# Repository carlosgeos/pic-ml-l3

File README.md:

# PIC ML-L3

Simple remote control for Nikon DSLR cameras.

## V1

## V2

### Schematic

### Operation

The micro is always sleeping. INT pin is connected to a momentary switch (push button) which triggers the interrupt service routine. The code executed in the ISR drives a BJT and the right pulses are sent to the IR LED.

### Measurements at 4.8V (3xAAA batteries)

- Total idle (sleep) current draw:
  - With power LED indicator: ~0.3mA
  - Without power LED indicator (MCU alone): 40uA
- Peak current through IR led: ~70mA

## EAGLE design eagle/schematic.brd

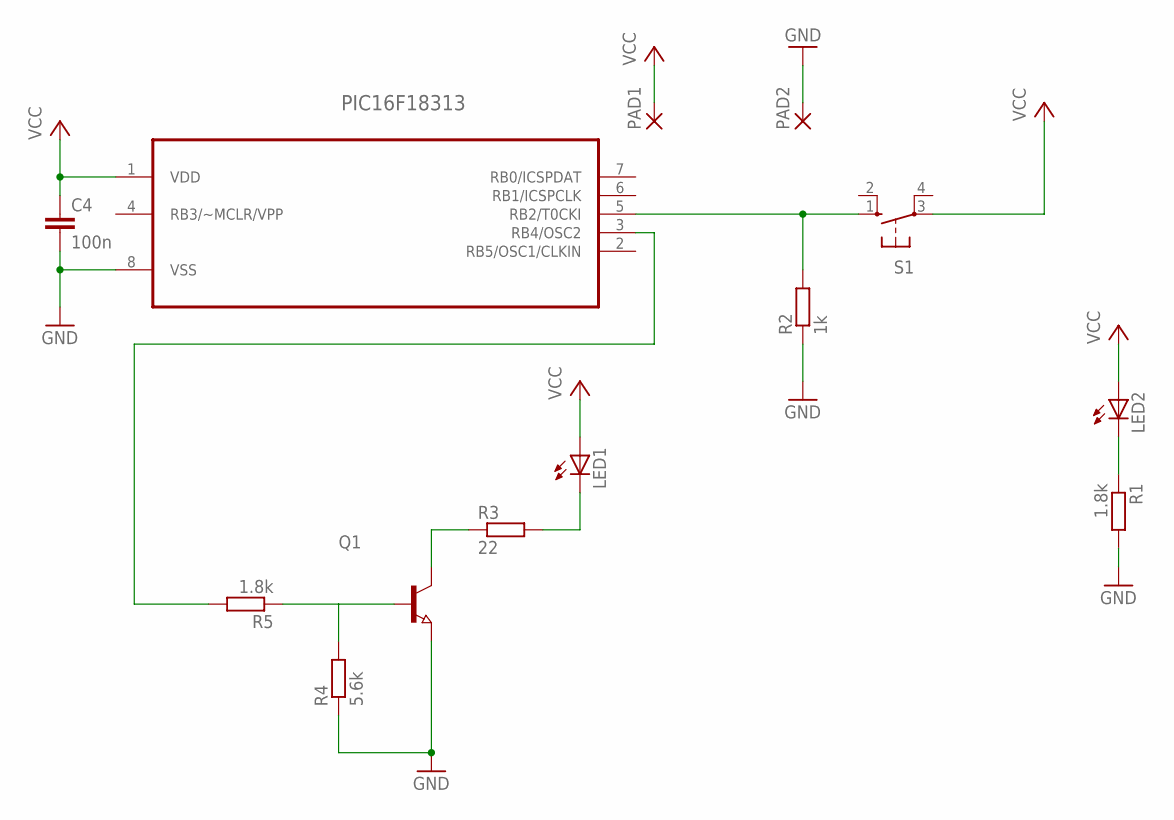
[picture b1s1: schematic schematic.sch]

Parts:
C4: 100n; C1206
LED1: LED3MM
LED2: LEDCHIPLED_1206; CHIPLED_1206
PAD1, PAD2: 2,54/0,9
PIC16F18313: PIC12F519-I/P; DIP254P762X533-8; MPN PIC18F18313-I/P
Q1: NPN-TRANSISTOR_SOT23; SOT23
R1, R5: 1.8k; M1206
R2: 1k; M1206
R3: 22; M1206
R4: 5.6k; M1206
S1: 10-XX; B3F-10XX

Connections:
GND: C4.2, PAD2.1, PIC16F18313.8 (VSS), Q1.2 (E), R1.2, R2.1, R4.1
unnamed: PIC16F18313.3 (RB4/OSC2), R5.2
unnamed: PIC16F18313.5 (RB2/T0CKI), R2.2, S1.1 (S)
unnamed: Q1.3 (C), R3.1
unnamed: LED1.K (C), R3.2
unnamed: LED2.C, R1.1
unnamed: Q1.1 (B), R4.2, R5.1
VCC: C4.1, LED1.A, LED2.A, PAD1.1, PIC16F18313.1 (VDD), S1.3

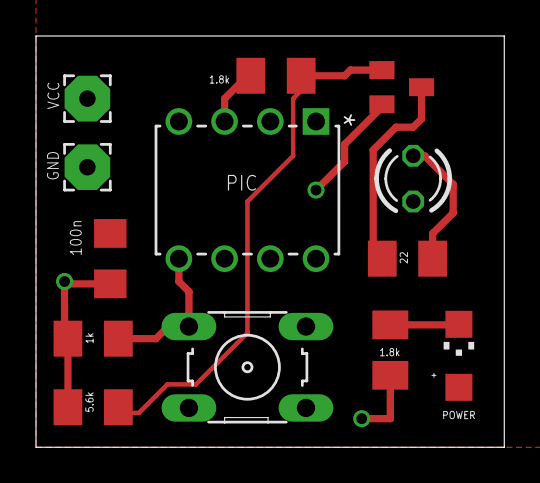
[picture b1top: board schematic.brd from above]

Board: 2 copper layers, 26.0 x 22.8 mm, 13 parts (0 on the bottom side), 8 nets.

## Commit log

2017-01-31 Init and full commit
2017-04-30 v2 and eagle files
